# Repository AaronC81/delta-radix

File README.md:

# Delta Radix

**[Try it online!](https://aaronc81.github.io/delta-radix/)**

The Delta Radix is a desktop calculator designed specifically to be useful for binary and
hexadecimal calculations.

Notable features:

- Mixed binary, hexadecimal, and decimal calculations
- Customisable bit width of arithmetic type (not limited to powers of 2!)
- Support for signed and unsigned data types
- Accurate simulation of overflow 
- Mechanical keyswitches for input

## Software

This repository is a Cargo workspace comprising a handful of crates. These are:

- `delta-radix-os` - The user-facing calculator software, 100% hardware-agnostic
- `delta-radix-hal` - Traits which the OS uses to interact with hardware (keypad, display, etc)
- `delta-radix-hal-pico` - Implementation of HAL traits for the Raspberry Pi Pico
- `delta-radix-hal-sim` - Implementation of HAL traits for a simulator which runs in the terminal
- `delta-radix-hal-web` - Implementation of HAL traits for a browser-based simulator with WebAssembly
  (build with `wasm-pack build --target web`, then visit `index.html`)
- `flex-int` - Arbitrary-precision arithmetic library used by the OS

The HAL implementations are the executable targets which should be flashed/run.

Elsewhere, you'll also find:

- [`delta-radix-numworks`](https://github.com/AaronC81/delta-radix-numworks) - Implementation of HAL
  traits for an app on the NumWorks graphing calculator.
  - This is a separate repository because it's not a pure-Cargo project, rather a Rust static
    library linked against a supporting C binary.

## Hardware

`hardware/` contains a KiCad schematic and PCB design.

`cad/` contains a 3D-printable case which the PCB can be mounted into, and keycaps for the switches.

## Usage

**Note:** Arithmetic parsing is incomplete! While they are implemented in the arithmetic library,
there's no way to input operations other than addition yet.

Base specifiers can appear on either site of a number (`xCAFE` or `CAFEx`), whichever you prefer. A
number without a base specifier is always interpreted as a decimal.

To change the result base, press the Format Select (`->`) key and then the base you'd like. Press
the Format Select key twice to return to decimal.

To change the arithmetic data type, use the Menu key. Enter a number of bits, and use the `+`/`-`
keys to choose signed or unsigned respectively.

Shift > Menu shows a menu of meta options, such as entering the bootloader.

## Things left to do

- [X] Faster parsing mode for constant overflow warnings
  - Parsing is slow, largely because of `FlexInt::from_unsigned_decimal_string` 
  - Wouldn't be a problem for evaluation, but is annoying during editing (key-press lag)
  - Either add a faster overall parsing mode just for constant overflow warnings, or versions of 
    number parsing which aren't suitable for evaluation but are fine for warnings (e.g. just use
    built-in Rust parsing, don't calculate overflow)
- [X] "Clear" key (shift + del?)
- [ ] Variables
- [X] Parentheses
- [X] Scrolling expression input
- [X] Show result as if unsigned
- [X] Sleep after inactivity

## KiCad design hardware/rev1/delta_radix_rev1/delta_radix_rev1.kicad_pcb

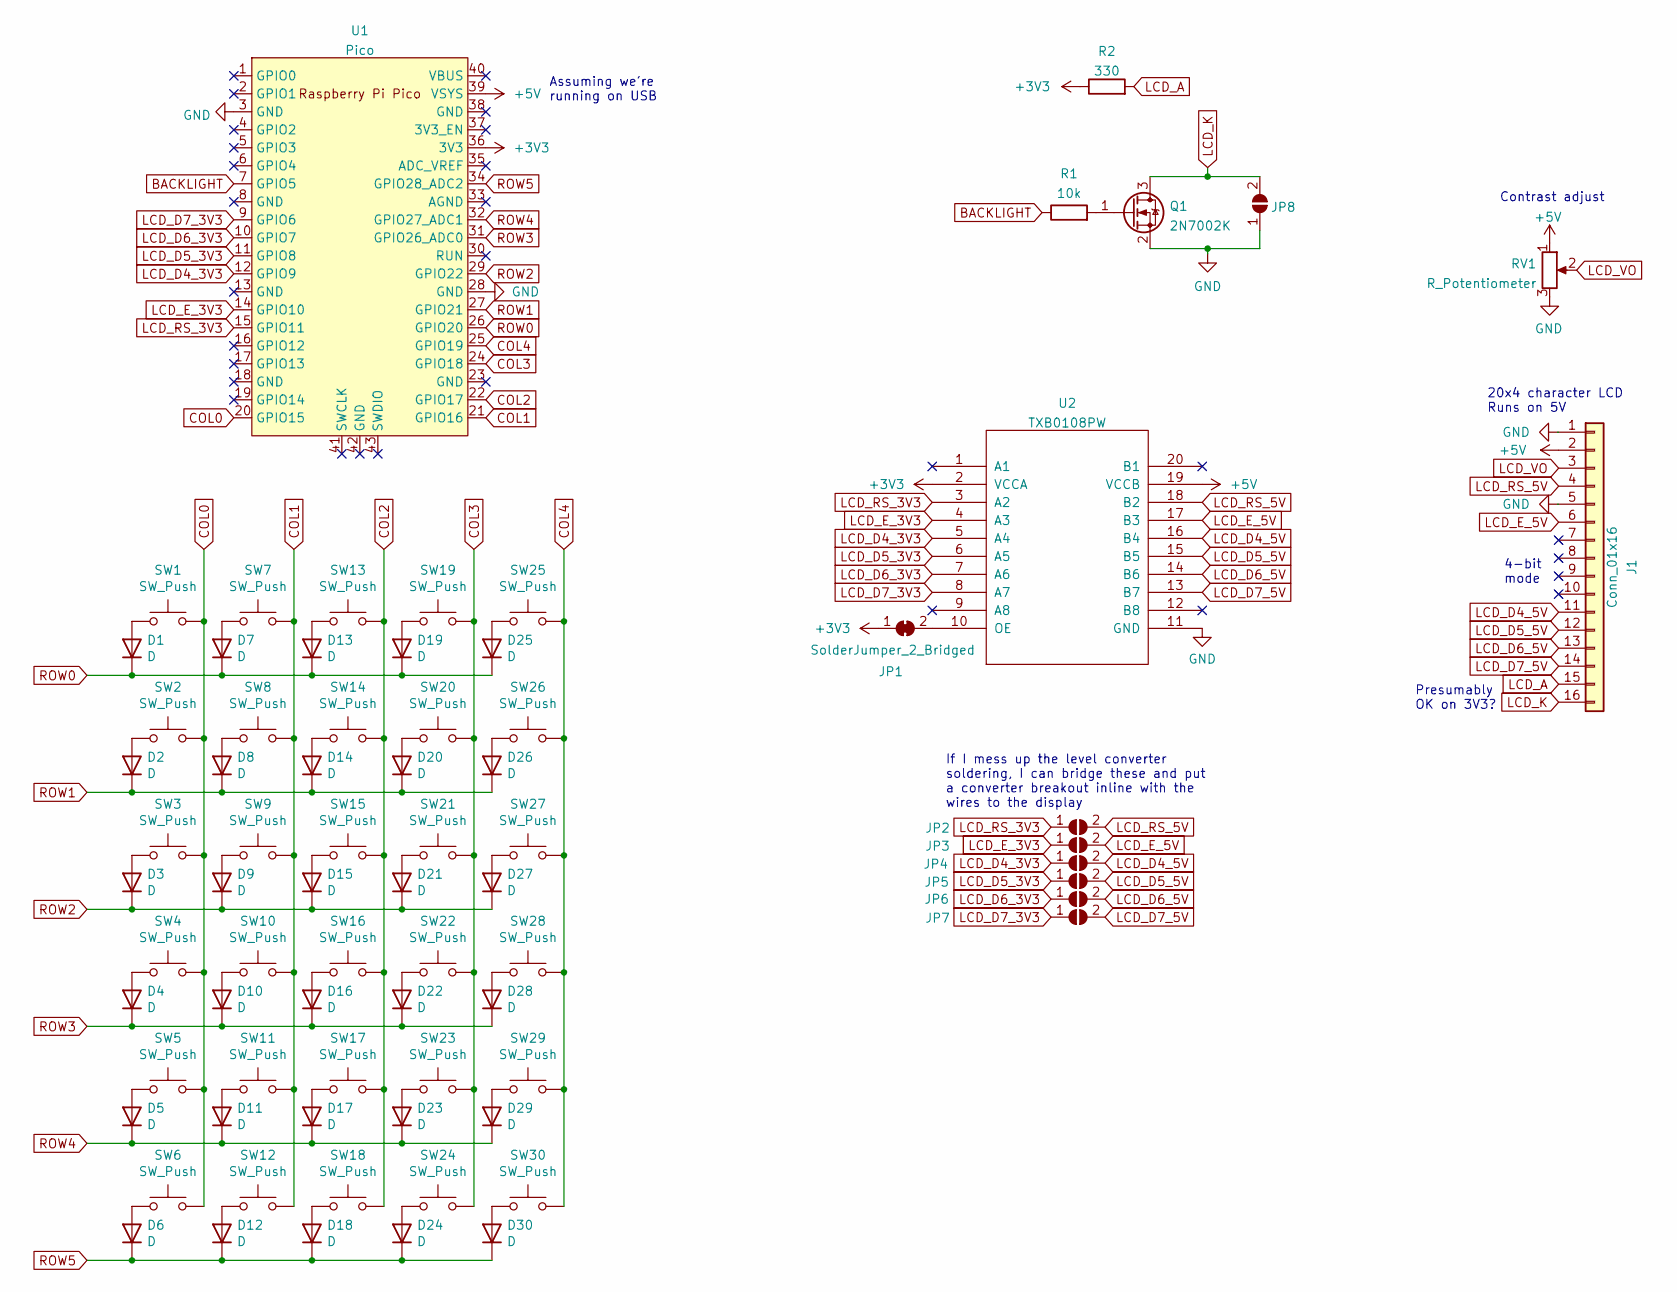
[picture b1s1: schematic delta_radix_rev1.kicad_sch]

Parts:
D1, D2, D3, D4, D5, D6, D7, D8, D9, D10, D11, D12, D13, D14, D15, D16, D17, D18, D19, D20, D21, D22, D23, D24, D25, D26, D27, D28, D29, D30: D; D_SOD-123
J1: Conn_01x16; PinHeader_1x16_P2.54mm_Vertical
JP1: SolderJumper_2_Bridged; SolderJumper-2_P1.3mm_Bridged_RoundedPad1.0x1.5mm
JP2, JP3, JP4, JP5, JP6, JP7, JP8: SolderJumper_2_Open; SolderJumper-2_P1.3mm_Open_RoundedPad1.0x1.5mm
Q1: 2N7002K; SOT-23_Handsoldering
R1: 10k; R_0603_1608Metric_Pad0.98x0.95mm_HandSolder
R2: 330; R_0603_1608Metric_Pad0.98x0.95mm_HandSolder
RV1: R_Potentiometer; Potentiometer_Alpha_RD901F-40-00D_Single_Vertical_CircularH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
SW1, SW2, SW3, SW4, SW5, SW6, SW7, SW8, SW9, SW10, SW11, SW12, SW13, SW14, SW15, SW16, SW17, SW18, SW19, SW20, SW21, SW22, SW23, SW24, SW25, SW26, SW27, SW28, SW29, SW30: SW_Push; SW_Cherry_MX_1.00u_PCB
U1: Pico; RPi_Pico_SMD_TH
U2: TXB0108PW; TSSOP-20_4.4x6.5mm_P0.65mm

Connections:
+3V3: JP1.1 (A), R2.1, U1.36 (3V3), U2.2 (VCCA)
+5V: J1.2, RV1.1, U1.39 (VSYS), U2.19 (VCCB)
BACKLIGHT: R1.1, U1.7 (GPIO5)
COL0: SW1.2, SW2.2, SW3.2, SW4.2, SW5.2, SW6.2, U1.20 (GPIO15)
COL1: SW7.2, SW8.2, SW9.2, SW10.2, SW11.2, SW12.2, U1.21 (GPIO16)
COL2: SW13.2, SW14.2, SW15.2, SW16.2, SW17.2, SW18.2, U1.22 (GPIO17)
COL3: SW19.2, SW20.2, SW21.2, SW22.2, SW23.2, SW24.2, U1.24 (GPIO18)
COL4: SW25.2, SW26.2, SW27.2, SW28.2, SW29.2, SW30.2, U1.25 (GPIO19)
GND: J1.1, J1.5, JP8.1 (A), Q1.2 (S), RV1.3, U1.3 (GND), U1.28 (GND), U2.11 (GND)
LCD_A: J1.15, R2.2
LCD_D4_3V3: JP4.1 (A), U1.12 (GPIO9), U2.5 (A4)
LCD_D4_5V: J1.11, JP4.2 (B), U2.16 (B4)
LCD_D5_3V3: JP5.1 (A), U1.11 (GPIO8), U2.6 (A5)
LCD_D5_5V: J1.12, JP5.2 (B), U2.15 (B5)
LCD_D6_3V3: JP6.1 (A), U1.10 (GPIO7), U2.7 (A6)
LCD_D6_5V: J1.13, JP6.2 (B), U2.14 (B6)
LCD_D7_3V3: JP7.1 (A), U1.9 (GPIO6), U2.8 (A7)
LCD_D7_5V: J1.14, JP7.2 (B), U2.13 (B7)
LCD_E_3V3: JP3.1 (A), U1.14 (GPIO10), U2.4 (A3)
LCD_E_5V: J1.6, JP3.2 (B), U2.17 (B3)
LCD_K: J1.16, JP8.2 (B), Q1.3 (D)
LCD_RS_3V3: JP2.1 (A), U1.15 (GPIO11), U2.3 (A2)
LCD_RS_5V: J1.4, JP2.2 (B), U2.18 (B2)
LCD_VO: J1.3, RV1.2
unnamed: D1.2 (A), SW1.1
unnamed: D2.2 (A), SW2.1
unnamed: D3.2 (A), SW3.1
unnamed: D4.2 (A), SW4.1
unnamed: D5.2 (A), SW5.1
unnamed: D6.2 (A), SW6.1
unnamed: D7.2 (A), SW7.1
unnamed: D8.2 (A), SW8.1
unnamed: D9.2 (A), SW9.1
unnamed: D10.2 (A), SW10.1
unnamed: D11.2 (A), SW11.1
unnamed: D12.2 (A), SW12.1
unnamed: D13.2 (A), SW13.1
unnamed: D14.2 (A), SW14.1
unnamed: D15.2 (A), SW15.1
unnamed: D16.2 (A), SW16.1
unnamed: D17.2 (A), SW17.1
unnamed: D18.2 (A), SW18.1
unnamed: D19.2 (A), SW19.1
unnamed: D20.2 (A), SW20.1
unnamed: D21.2 (A), SW21.1
unnamed: D22.2 (A), SW22.1
unnamed: D23.2 (A), SW23.1
unnamed: D24.2 (A), SW24.1
unnamed: D25.2 (A), SW25.1
unnamed: D26.2 (A), SW26.1
unnamed: D27.2 (A), SW27.1
unnamed: D28.2 (A), SW28.1
unnamed: D29.2 (A), SW29.1
unnamed: D30.2 (A), SW30.1
unnamed: JP1.2 (B), U2.10 (OE)
unnamed: Q1.1 (G), R1.2
ROW0: D1.1 (K), D7.1 (K), D13.1 (K), D19.1 (K), D25.1 (K), U1.26 (GPIO20)
ROW1: D2.1 (K), D8.1 (K), D14.1 (K), D20.1 (K), D26.1 (K), U1.27 (GPIO21)
ROW2: D3.1 (K), D9.1 (K), D15.1 (K), D21.1 (K), D27.1 (K), U1.29 (GPIO22)
ROW3: D4.1 (K), D10.1 (K), D16.1 (K), D22.1 (K), D28.1 (K), U1.31 (GPIO26_ADC0)
ROW4: D5.1 (K), D11.1 (K), D17.1 (K), D23.1 (K), D29.1 (K), U1.32 (GPIO27_ADC1)
ROW5: D6.1 (K), D12.1 (K), D18.1 (K), D24.1 (K), D30.1 (K), U1.34 (GPIO28_ADC2)

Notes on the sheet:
Contrast adjust
Presumably OK on 3V3?
4-bit mode
If I mess up the level converter soldering, I can bridge these and put a converter breakout inline with the wires to the display
20x4 character LCD Runs on 5V
Assuming we're running on USB

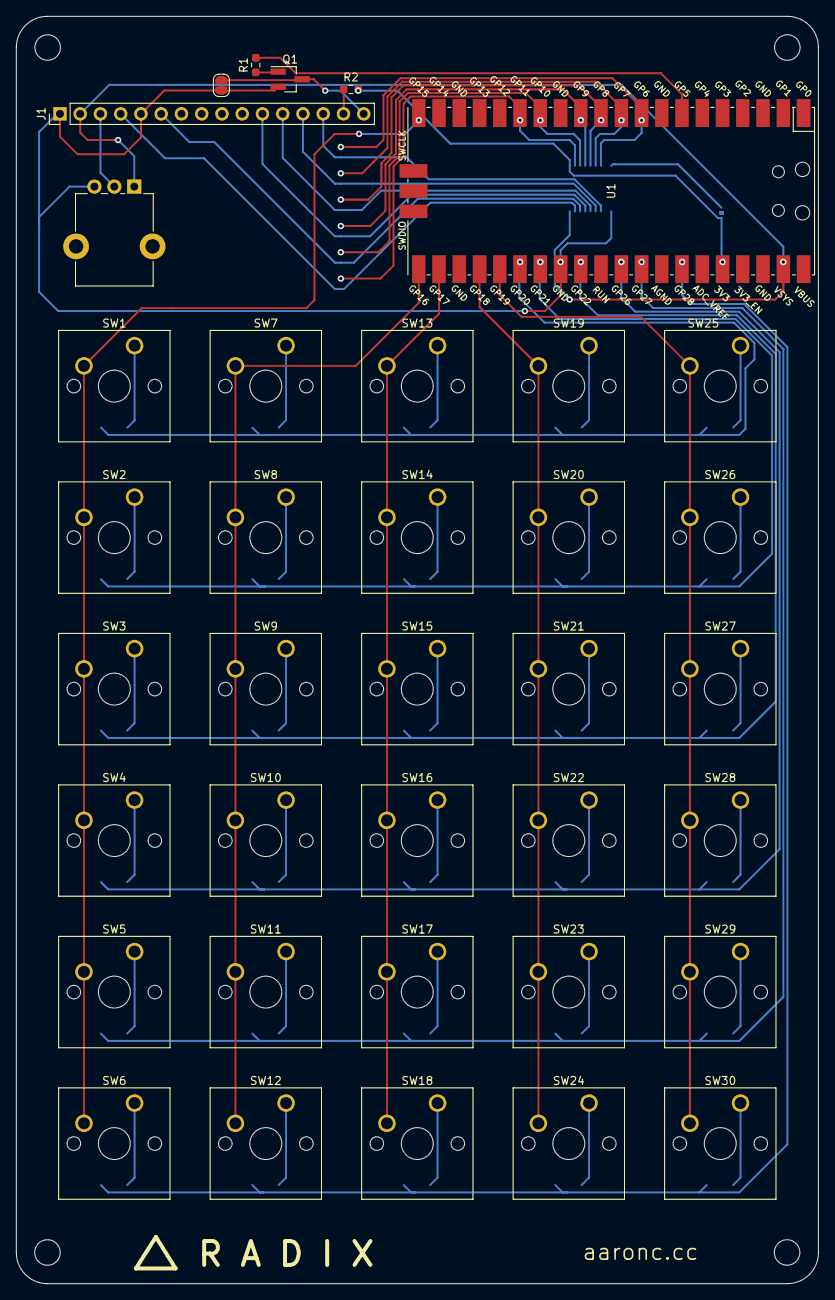
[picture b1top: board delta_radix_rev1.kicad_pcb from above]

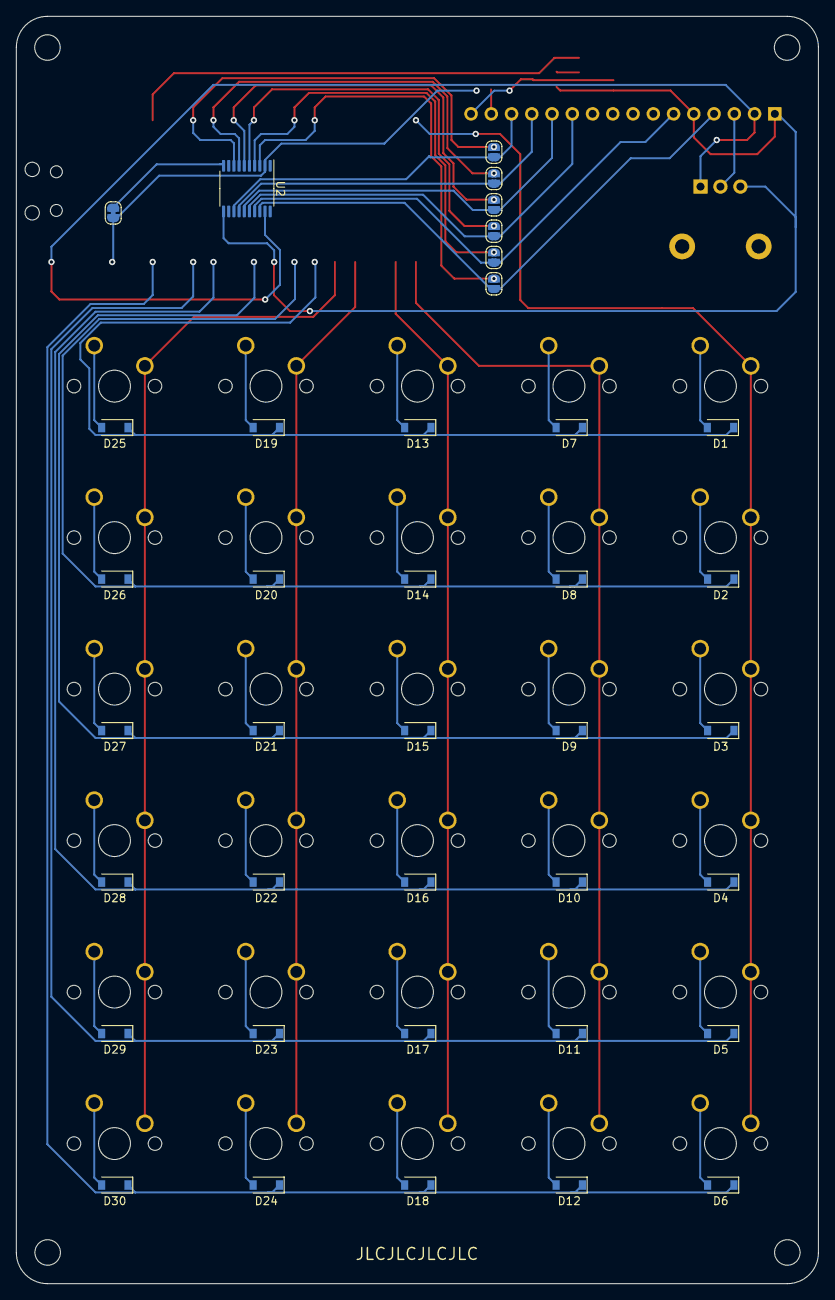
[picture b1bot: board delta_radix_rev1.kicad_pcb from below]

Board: 2 copper layers, 100.6 x 159.0 mm, 75 parts (38 on the bottom side), 62 nets.

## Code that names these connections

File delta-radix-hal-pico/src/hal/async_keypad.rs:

use delta_radix_hal::{Key, Keypad, Display};
use embedded_hal::digital::v2::OutputPin;
use embedded_time::duration::{Extensions, Duration, Seconds, Microseconds};
use rp_pico::{pac::{self, interrupt}, hal::{Sio, multicore::Stack, sio::SioFifo, timer::Alarm0, Timer}, Pins};

use crate::{lives_forever, executor, panic::get_panic_hal};

use super::ButtonMatrix;

pub struct AsyncKeypadReceiver<'s> {
    pub fifo: &'s mut SioFifo,
}

impl<'s> delta_radix_hal::Keypad for AsyncKeypadReceiver<'s> {
    async fn wait_key(&mut self) -> Key {
        let hal = get_panic_hal();

        loop {
            let message = self.fifo.read_blocking();

            if message == ASYNC_KEYPAD_SLEEP_MAGIC {
                hal.display.clear();
                hal.display.backlight.set_low().unwrap();

                return Key::Sleep;
            }

            if let Some(key) = Key::from_u32(message) {
                hal.display.backlight.set_high().unwrap();
                return key;
            }
        }
    }
}

pub const ASYNC_KEYPAD_START_MAGIC: u32 = 0xCAFECAFE;
pub const ASYNC_KEYPAD_SLEEP_MAGIC: u32 = 0x00BEDBED;

pub const SLEEP_TIME: Microseconds = Microseconds(120_000_000);

pub fn async_keypad_core1() -> ! {
    // Grab some important peripherals
    let mut pac = unsafe { pac::Peripherals::steal() };
    let core = unsafe { pac::CorePeripherals::steal() };
    let mut sio = Sio::new(pac.SIO);
    let mut delay = cortex_m::delay::Delay::new(core.SYST, 125_000_000);
    let pins = Pins::new(
        pac.IO_BANK0,
        pac.PADS_BANK0,
        sio.gpio_bank0,
        &mut pac.RESETS,
    );

    // Wait until the magic word over FIFO
    loop {
        if sio.fifo.read_blocking() == ASYNC_KEYPAD_START_MAGIC {
            break;
        }
    }

    // Set up button matrix
    let mut matrix = ButtonMatrix {
        delay: lives_forever(&mut delay),

        col0: pins.gpio15.into_pull_up_input(),
        col1: pins.gpio16.into_pull_up_input(),
        col2: pins.gpio17.into_pull_up_input(),
        col3: pins.gpio18.into_pull_up_input(),
        col4: pins.gpio19.into_pull_up_input(),

        row0: pins.gpio20.into_push_pull_output(),
        row1: pins.gpio21.into_push_pull_output(),
        row2: pins.gpio22.into_push_pull_output(),
        row3: pins.gpio26.into_push_pull_output(),
        row4: pins.gpio27.into_push_pull_output(),
        row5: pins.gpio28.into_push_pull_output(),

        currently_pressed: None,
    };

    // Set up timer stuff
    unsafe { pac::NVIC::unmask(pac::Interrupt::TIMER_IRQ_0); }
    let mut timer = Timer::new(pac.TIMER, &mut pac.RESETS);
    let mut alarm = timer.alarm_0().unwrap();
    
    // For the rest of time, loop looking for buttons
    loop {
        // Set up inactivity timer
        alarm.disable_interrupt();
        alarm.schedule(SLEEP_TIME).unwrap();
        alarm.enable_interrupt();
    
        // Wait for press
        let key = executor::execute(matrix.wait_key());
        sio.fifo.write(key.to_u32());
    }
}

#[interrupt]
fn TIMER_IRQ_0() {
    let mut pac = unsafe { pac::Peripherals::steal() };
    let mut sio = Sio::new(pac.SIO);

    // Let the other core know to put the display into a sleep state
    sio.fifo.write(ASYNC_KEYPAD_SLEEP_MAGIC);

    let mut timer = Timer::new(pac.TIMER, &mut pac.RESETS);
    let mut alarm = timer.alarm_0().unwrap();
    alarm.clear_interrupt();
}

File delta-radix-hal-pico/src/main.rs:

#![no_std]
#![no_main]
#![feature(alloc_error_handler)]
#![feature(generic_const_exprs)]
#![feature(async_fn_in_trait)]

use alloc_cortex_m::CortexMHeap;
use cortex_m_rt::entry;
use delta_radix_hal::Key;
use embedded_hal::digital::v2::OutputPin;
use hal::{PicoHal, async_keypad::{async_keypad_core1, AsyncKeypadReceiver, ASYNC_KEYPAD_START_MAGIC}};
use hd44780_driver::HD44780;
use panic::init_panic_hal;
use rp_pico::{hal::{Watchdog, Sio, clocks::init_clocks_and_plls, Clock, multicore::{Stack, Multicore}}, pac, Pins};
use embedded_time::{fixed_point::FixedPoint};

extern crate alloc;

mod hal;
mod panic;
mod executor;

fn lives_forever<T: ?Sized>(t: &mut T) -> &'static mut T {
    unsafe { (t as *mut T).as_mut().unwrap() }
}

#[global_allocator]
static ALLOCATOR: CortexMHeap = CortexMHeap::empty();
const HEAP_SIZE: usize = 230_000;

static mut CORE1_STACK: Stack<4096> = Stack::new();

#[entry]
fn main() -> ! {
    // Set up allocator
    {
        use core::mem::MaybeUninit;
        static mut HEAP: [MaybeUninit<u8>; HEAP_SIZE] = [MaybeUninit::uninit(); HEAP_SIZE];
        unsafe {
            ALLOCATOR.init(HEAP.as_ptr() as usize, HEAP_SIZE)
        }
    }

    let mut pac = pac::Peripherals::take().unwrap();
    let core = pac::CorePeripherals::take().unwrap();
    let mut watchdog = Watchdog::new(pac.WATCHDOG);
    let mut sio = Sio::new(pac.SIO);

    let mut mc = Multicore::new(&mut pac.PSM, &mut pac.PPB, &mut sio);
    let cores = mc.cores();
    let core1 = &mut cores[1];
    let _test = core1.spawn(async_keypad_core1, unsafe { &mut CORE1_STACK.mem });

    // External high-speed crystal on the pico board is 12Mhz
    let external_xtal_freq_hz = 12_000_000u32;
    let clocks = init_clocks_and_plls(
        external_xtal_freq_hz,
        pac.XOSC,
        pac.CLOCKS,
        pac.PLL_SYS,
        pac.PLL_USB,
        &mut pac.RESETS,
        &mut watchdog,
    )
        .ok()
        .unwrap();

    let mut delay = cortex_m::delay::Delay::new(core.SYST, clocks.system_clock.freq().integer());

    let pins = Pins::new(
        pac.IO_BANK0,
        pac.PADS_BANK0,
        sio.gpio_bank0,
        &mut pac.RESETS,
    );
    let mut led = pins.led.into_push_pull_output();

    let mut backlight = pins.gpio5.into_push_pull_output();
    backlight.set_high().unwrap();

    // const int rs = 11, en = 10, d4 = 9, d5 = 8, d6 = 7, d7 = 6;
    let rs = pins.gpio11.into_push_pull_output();
    let en = pins.gpio10.into_push_pull_output();
    let d4 = pins.gpio9.into_push_pull_output();
    let d5 = pins.gpio8.into_push_pull_output();
    let d6 = pins.gpio7.into_push_pull_output();
    let d7 = pins.gpio6.into_push_pull_output();
    
    let lcd = HD44780::new_4bit(rs, en, d4, d5, d6, d7, &mut delay).unwrap();

    let mut hal = PicoHal {
        display: hal::LcdDisplay { lcd, delay: lives_forever(&mut delay), backlight },
        keypad: AsyncKeypadReceiver {
            fifo: lives_forever(&mut sio.fifo),
        },
        time: hal::DelayTime { delay: lives_forever(&mut delay) },
    };
    init_panic_hal(lives_forever(&mut hal));

    // Tell the other core to get going
    sio.fifo.write(ASYNC_KEYPAD_START_MAGIC);    

    executor::execute(delta_radix_os::main(&mut hal));
    
    loop {
        led.set_high().unwrap();
        delay.delay_ms(1000);
        led.set_low().unwrap();
        delay.delay_ms(1000);
    }
}

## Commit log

2023-01-18 Add delta-radix-os
2023-01-19 Add simulator implementation of HAL
2023-01-19 Draw border around display
2023-01-19 Make HAL access neater, add a splash screen to OS
2023-01-19 Add display clearing
2023-01-20 Add start of calculator frontend
2023-01-20 Add cursor movement and more glyphs
2023-01-20 Add arbitrary-size binary integer type
2023-01-21 Add loads more operations to FlexInt
2023-01-21 Make `add` take signedness too
2023-01-21 Implement `from_decimal_string`
2023-01-21 Start adding parsing and evaluation
2023-01-22 Start adding evaluation from UI
2023-01-22 Add `hardware` to gitignore for now
    Just playing around with stuff
2023-01-25 Add delta-radix-hal-pico project
2023-01-25 Implement basics of HAL for Pico
    Gets to a mangled version of the "Press a key" screen!
2023-01-27 Fix display position setting
2023-01-27 Break out HAL into separate files
2023-01-27 Add working keypad input
    Surprisingly painless!
2023-01-27 "Fix" cursor appearance on hardware
2023-01-27 Add bootloader button
2023-01-27 Fix some warnings
2023-01-27 Add hexadecimal parsing
2023-01-27 Show overflow marker
2023-01-30 Use own fork of hd44780-driver
2023-01-30 Add key press tracking
2023-01-30 Init the screen correctly
2023-01-30 Use custom characters for cursor
2023-01-30 Tidy up special character system, add them for warnings
2023-01-30 Add left and right keys
2023-01-30 Add custom characters for cursor with warning
2023-01-31 Exclude /cad until I've tidied it up a bit
2023-01-31 Remove addressed TODO
2023-01-31 Add add/sub parsing
2023-01-31 Add a + key
2023-01-31 Right-align result
2023-02-03 Turn on the backlight
    ...because hardware backlight control *works*! Yeaahhhh
2023-02-03 Use keys on rev 1
    Well, except the bootloader one
2023-02-05 Break out FlexInt into a library crate
2023-02-06 Begin adding a fuzzer for flex-int
2023-02-06 Add operation system to fuzzing
2023-02-06 Add fuzzing for u8 and unsigned subtraction
2023-02-06 Add experimental subtract_signed
2023-02-07 Add signed string conversions, prepare fuzzer for them
2023-02-07 Fuzz for i8s
2023-02-07 Fix negation of 0 causing panic
2023-02-07 Fix overflow detection when adding a negative number
2023-02-08 Fix subtracting the most unsigned number
2023-02-09 Add `FlexInt::subtract`
2023-02-09 Fuzz multiplication
2023-02-09 Add additional overflow check for signed multiplication
2023-02-10 Fuzz division
2023-02-10 Handle div-by-zero by returning 0 and overflow
2023-02-11 Add base keys
2023-02-11 Add hexadecimal digit input and display
2023-02-11 Error gracefully on number parse failures
2023-02-11 Begin scaffolding format selection
    Converting into hex/binary not actually implemented yet
2023-02-11 Add unsigned hex string conversion
2023-02-11 Break out some common string conversion logic, fix tests
    Whoops!
2023-02-11 Fix fuzzer divsion failure
2023-02-11 Add signed variant of hex string conversion
2023-02-11 Implement hex output display using new string methods
2023-02-11 More permissive key release logic
    This makes the keypad feel *much* more responsive if you're pressing quickly!
    Now, when waiting for a release, we wait for either a release **or a different key**
    This means you can press another key before fully releasing the first
2023-02-12 Add a menu to access the bootloader
2023-02-12 Remove splash screen
2023-02-12 Add shift key
2023-02-12 Add menu to change evaluation settings
2023-02-14 Fix returning to normal mode after format select
2023-02-14 Add case models
2023-02-14 Add KiCad design
2023-02-14 Add README
2023-02-14 Update keypad ordering
2023-02-15 Start creating web simulator
2023-02-15 Scaffold a bindgen approach instead
    Maybe easier?
2023-02-15 Attempt to bind HAL to JS functions
    Fails to compile right now for some reason!
2023-02-15 Ah, that's it - you can't have a function named `main`
2023-02-15 Working display implementation
2023-02-15 Working keypad key!
2023-02-15 All buttons, and *style*
2023-02-16 Use non-breaking spaces when clearing
2023-02-16 Update README for delta-radix-hal-web
2023-02-16 Add GitHub actions to deploy web simulator
2023-02-16 Use `working-directory`
2023-02-16 Use nightly Rust
2023-02-16 Add link to simulator
2023-02-16 Test signed integer parsing overflow
    I thought this was broken, but the test is fine!
    Must be something else
2023-02-16 Fix signed number parsing
2023-02-16 Fix some clippy lints
2023-02-16 Fix rust-analyser error, fix more warnings
2023-02-17 Implement evaluation for all nodes (though no parsing yet)
2023-02-17 Implement mul, div, and unary negation
2023-02-17 Refactor glyphs to let HALs override how they're drawn
2023-02-17 Better parse error messages
2023-02-17 Parse nothing as 0
2023-02-17 Fix parsing bug which made "2+2" invalid
    lol
2023-02-18 Begin adding a HAL for usage in automated tests
2023-02-18 Don't need OS to own HAL
2023-02-18 Add a "pretend key" which panics the OS
2023-02-18 Add first calc test
2023-02-18 Add a cleaner way of doing keys, new test case
2023-02-18 Add some tests for hex number parsing
2023-02-18 Refactor FlexInt into multiple files
2023-02-18 Add binary string conversions
2023-02-18 Add binary input/output
2023-02-18 Remove long-addressed TODO
2023-02-18 Enter bootloader on panic
2023-02-18 Fix missing unsafe
2023-02-20 Add keypad <-/-> SIO conversion
2023-02-20 Start adding multicore input
    Can receive input over SIO but not when other core started
2023-02-21 Fillets, tolerance tweaks, and logo for bottom case
2023-02-21 Allow us delays
2023-02-21 Heavily reduce debounce time Seems fine!
2023-02-21 Add panic messages to LCD
2023-02-22 Add fillet to top case
2023-02-22 Add reset button hole
2023-02-22 Cut out chunk around the display to save filament
2023-02-22 Add a dirty hand-written executor
2023-02-22 Re-enable multicore with smaller heap
    Seems to magically fix things!
2023-02-23 Use new executor, wait for special message before starting
    I've figured out where the problem is, at least...
    (Because I can now see the panic message!)
    alloc-cortex-m uses `RefCell`s so we can't alloc in two cores simultaneously
    It's not trivial to remove allocations because `async_trait` desugars to `Box<Pin<...>>`
    Might need a different allocator :(
2023-02-23 Use nightly async traits, with no box allocation - now working!
    Also changed a heap pin to a stack pin in async_keypad.rs
    Still need to migrate other HAL crates over to native async traits
2023-02-23 Use native async traits everywhere
2023-02-23 Add BOOTSEL pusher
2023-02-23 Fix tests by adding async_fn_in_trait attribute
2023-02-23 Add a todo list
2023-02-23 Add another todo
2023-02-23 Add a "clear" key
2023-02-24 Add customisable number parsing
    This'll be useful later!
2023-02-24 Add faster number parser just for constant overflow checking
2023-02-24 Make spans cover unary negations
2023-02-24 Refactor out magic number
2023-02-25 Working experiment - schedule alarm to press some keys
2023-02-25 Change display after timeout
2023-02-25 Turn backlight off instead
2023-02-25 Clear some state when entering sleep
2023-02-25 Increase sleep time to 2 minutes
2023-02-25 Add test for something which is now not working
2023-02-25 Fix constant overflow not counting towards global overflow
2023-02-25 Tick off TODO
2023-02-25 Key mapping change
    Menu opens format select
    Shift > Menu opens bootloader menu
2023-02-25 Add horizontal scrolling
2023-02-25 Make constant overflow behaviour catch `from_str_radix` overflows
2023-02-25 Shift+0 to insert parens
    Don't parse yet
2023-02-25 Use * instead of unicode multiply for glyph print default
    So it's only one byte
2023-02-25 Add parenthesis parsing
2023-02-25 Tick off README item
2023-02-25 Add multiply symbol for Pico
2023-02-25 Add divide symbol
2023-02-25 Slightly nicer custom character API
2023-02-25 Bigger default size
2023-02-25 Add result-signedness override (currently not user-controllable)
2023-02-25 Add signedness override menu
2023-02-26 Begin adding variable usage in calculations
    Can't set them yet
2023-02-26 Put base marker on LHS
2023-02-26 Add variable setting
2023-02-26 Separate calc files into backend and frontend
2023-02-26 Break up frontend files
2023-02-26 Refactor out menu
2023-02-27 Fix panic when result is longer than the screen
2023-02-27 Fix base parsing
2023-02-27 Add variable view page
2023-02-28 Handle when the result is too big for one line
2023-08-30 Add `align` and `bitwise_and` to `FlexInt`
2023-08-30 Add input and evaluation for "align" operation
2023-08-30 Use infallible align algorithm which supports non-powers-of-2
2023-09-07 Fix align insertion
2023-12-29 Link to NumWorks project
